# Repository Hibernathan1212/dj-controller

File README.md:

# DJ Controller

A MIDI jogless DJ controller similar to the Native Instruments S8 and D2 and X1 and Z1. Planning for it to just be a midi controller with knobs for mixing and controlling loops as well as buttons for play/pausing and others usually found on dj decks. Follows a modular design with the deck modules (2 on other side) and the mixer module which will have controls for 4 audio channels.

## Features

- Fully modular system
- 4 Audio track/channel support

## CAD

Consists of a base and a top lid that slots in a lip on the base. PCB is mounted to the lid with m2 screws that go into the faders and with the mx switches.

Onshape links:
[mixer](https://cad.onshape.com/documents/8781b8df6f967f1c6b6a95c1/w/5dca202985c09c767b10b646/e/c48e65838657ec88be66024d?renderMode=0&uiState=69ec6b3885827e36fd861eb5)
[deck](https://cad.onshape.com/documents/3b76899a1a1bc1a557b73df0/w/7b184ec473bdbf4286da5afb/e/11b981bd57d3e8bda80cba54?renderMode=0&uiState=69ec6bb0fbe7b2effac84fa0)

## PCB

Made in Kicad

### Schematic

### PCB

## Firmware

Uses python with the usb midi library and adafruit to take the GPIO input and send midi signals back to the computer.

# BOM

| Product                   | Amount | Unit Cost (THB) | Price (THB) | Price (USD) | Link                                                                                                                                                                                                                                                                                                                                                                                                                                                                                                                                                                                                                                                                                           |
| ------------------------- | ------ | --------------- | ----------- | ----------- | ---------------------------------------------------------------------------------------------------------------------------------------------------------------------------------------------------------------------------------------------------------------------------------------------------------------------------------------------------------------------------------------------------------------------------------------------------------------------------------------------------------------------------------------------------------------------------------------------------------------------------------------------------------------------------------------------- |
| CD74HC4067M               | 4      |                 | 57.82       | 1.788156353 | [https://th.aliexpress.com/item/1005006425003395.html](https://th.aliexpress.com/item/1005006425003395.html?spm=a2g0o.productlist.main.2.6875sBl8sBl8y9&algo_pvid=16e1eb5c-5f24-4909-9ec4-1832ca5d62b9&algo_exp_id=16e1eb5c-5f24-4909-9ec4-1832ca5d62b9-4&pdp_ext_f=%7B%22order%22%3A%2234%22%2C%22eval%22%3A%221%22%2C%22fromPage%22%3A%22search%22%7D&pdp_npi=6%40dis%21THB%21100.21%21100.21%21%21%2120.51%2120.51%21%402151e6dc17771029748282697e9e67%2112000037118555222%21sea%21TH%210%21ABX%211%210%21n_tag%3A-29910%3Bd%3A4d9dae13%3Bm03_new_user%3A-29895&curPageLogUid=p7QdqC5pT68Q&utparam-url=scene%3Asearch%7Cquery_from%3A%7Cx_object_id%3A1005006425003395%7C_p_origin_prod%3A) |
| bourn pta6043             | 2      | 62.9            | 125.8       | 3.890523508 | [https://th.element14.com/bourns/pta6043-2015dpb103/potentiometer-slide-10k-20-0-25w/dp/1688411](https://th.element14.com/bourns/pta6043-2015dpb103/potentiometer-slide-10k-20-0-25w/dp/1688411)                                                                                                                                                                                                                                                                                                                                                                                                                                                                                               |
| bourn pta4543             | 5      | 53.73           | 268.65      | 8.308339749 | [https://th.element14.com/bourns/pta4543-2015dpb103/potentiometer-slide-10k-45mm/dp/1688415](https://th.element14.com/bourns/pta4543-2015dpb103/potentiometer-slide-10k-45mm/dp/1688415)                                                                                                                                                                                                                                                                                                                                                                                                                                                                                                       |
| bourns ptv09a             | 27     | 23.36           | 630.72      | 19.50581071 | [https://th.element14.com/bourns/ptv09a-4020f-b103/pot-rotary-10kohm-9mm-20/dp/2469524](https://th.element14.com/bourns/ptv09a-4020f-b103/pot-rotary-10kohm-9mm-20/dp/2469524)                                                                                                                                                                                                                                                                                                                                                                                                                                                                                                                 |
| 100nf 0805 smd capacitors | 10     | 0.43            | 4.3         | 0.132982918 | [https://th.element14.com/multicomp-pro/mc0805b104k250ct/cap-0-1-f-25v-10-x7r-0805/dp/1759166](https://th.element14.com/multicomp-pro/mc0805b104k250ct/cap-0-1-f-25v-10-x7r-0805/dp/1759166)                                                                                                                                                                                                                                                                                                                                                                                                                                                                                                   |
| 6 alps ec11               | 6      | 81.42           | 488.52      | 15.10809654 | [https://th.element14.com/alps/ec11k1524402/encoder-vertical-11mm-30det-15ppr/dp/2064998](https://th.element14.com/alps/ec11k1524402/encoder-vertical-11mm-30det-15ppr/dp/2064998)                                                                                                                                                                                                                                                                                                                                                                                                                                                                                                             |
| m2 screws                 |        |                 | 154.17      | 4.767901504 | [https://th.element14.com/multicomp-pro/mp007338/screw-pan-head-pozidriv-m2-12mm/dp/3755264](https://th.element14.com/multicomp-pro/mp007338/screw-pan-head-pozidriv-m2-12mm/dp/3755264)                                                                                                                                                                                                                                                                                                                                                                                                                                                                                                       |
| orpheus pico              | 3      | ?               | ?           | 0           |                                                                                                                                                                                                                                                                                                                                                                                                                                                                                                                                                                                                                                                                                                |
| cherry switches           | 40     | 60              | 240         | 7.4223024   | [https://www.lazada.co.th/products/pdp-i5447727976-s23110798561.html](https://www.lazada.co.th/products/pdp-i5447727976-s23110798561.html)                                                                                                                                                                                                                                                                                                                                                                                                                                                                                                                                                     |
| cherry keycaps            | 38     | 280             | 560         | 17.3187056  | [https://www.lazada.co.th/products/lao8-20-key-xda-profile-pbt-keycaps-mechanical-keyboard-1u-1-x-ball-print-blank-customized-keycaps-mx-switches-xda-heighth-i16128506172-s127061437599.html?](https://www.lazada.co.th/products/lao8-20-key-xda-profile-pbt-keycaps-mechanical-keyboard-1u-1-x-ball-print-blank-customized-keycaps-mx-switches-xda-heighth-i16128506172-s127061437599.html?)                                                                                                                                                                                                                                                                                                 |
| 3d print filament         | 0.5    | 680             | 340         | 10.5149284  | [https://www.lazada.co.th/products/creality-hyper-petg-3d-printing-filament-1kg-175mm-plastic-filament-for-3d-printers-i5896245685-s126802674906.html?](https://www.lazada.co.th/products/creality-hyper-petg-3d-printing-filament-1kg-175mm-plastic-filament-for-3d-printers-i5896245685-s126802674906.html?)                                                                                                                                                                                                                                                                                                                                                                                 |
| jlcpcb                    |        |                 |             | 33.94       |                                                                                                                                                                                                                                                                                                                                                                                                                                                                                                                                                                                                                                                                                                |
| element 14 deliv          |        |                 | 550         | 17.009443   |                                                                                                                                                                                                                                                                                                                                                                                                                                                                                                                                                                                                                                                                                                |
|                           |        |                 |             |             |                                                                                                                                                                                                                                                                                                                                                                                                                                                                                                                                                                                                                                                                                                |
| total                     |        |                 |             | 139.7071907 |

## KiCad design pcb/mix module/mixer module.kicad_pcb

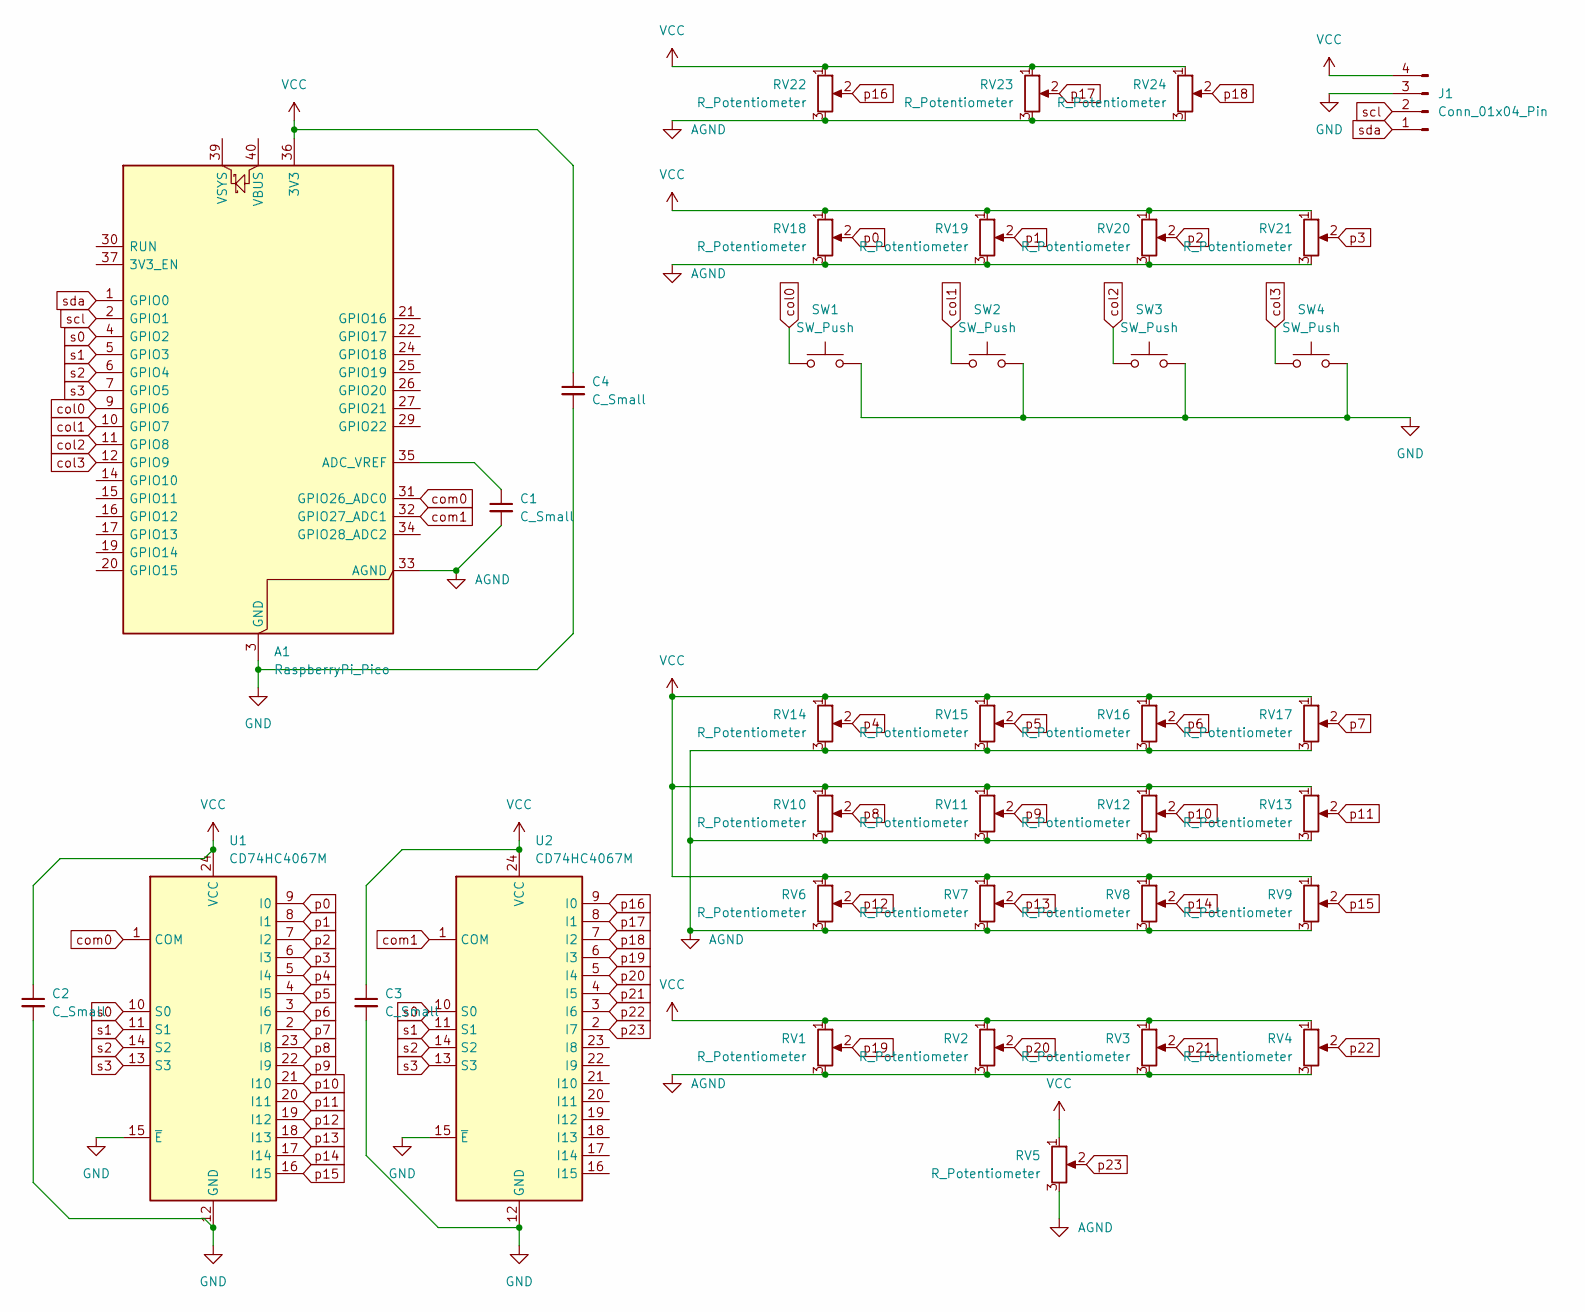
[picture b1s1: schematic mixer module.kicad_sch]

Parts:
A1: RaspberryPi_Pico; RaspberryPi_Pico_Common_Unspecified
C1, C2, C3, C4: C_Small; C_0805_2012Metric_Pad1.18x1.45mm_HandSolder
J1: Conn_01x04_Pin; ER_OLEDM0.91_1x-I2C
RV1, RV2, RV3, RV4, RV5: R_Potentiometer; Potentiometer_Bourns_PTA4543_Single_Slide
RV6, RV7, RV8, RV9, RV10, RV11, RV12, RV13, RV14, RV15, RV16, RV17, RV18, RV19, RV20, RV21, RV22, RV23, RV24: R_Potentiometer; Potentiometer_Bourns_PTV09A-1_Single_Vertical
SW1, SW2, SW3, SW4: SW_Push; SW_Cherry_MX_1.00u_PCB
U1, U2: CD74HC4067M; SOIC-24W_7.5x15.4mm_P1.27mm

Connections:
AGND: A1.33 (AGND), C1.2, RV1.3, RV2.3, RV3.3, RV4.3, RV5.3, RV6.3, RV7.3, RV8.3, RV9.3, RV10.3, RV11.3, RV12.3, RV13.3, RV14.3, RV15.3, RV16.3, RV17.3, RV18.3, RV19.3, RV20.3, RV21.3, RV22.3, RV23.3, RV24.3
GND: A1.3 (GND), A1.8 (GND), A1.13 (GND), A1.18 (GND), A1.23 (GND), A1.28 (GND), A1.38 (GND), C2.2, C3.2, C4.2, J1.3, SW1.2, SW2.2, SW3.2, SW4.2, U1.12 (GND), U1.15 (~E), U2.12 (GND), U2.15 (~E)
unnamed: A1.35 (ADC_VREF), C1.1
VCC: A1.36 (3V3), C2.1, C3.1, C4.1, J1.4, RV1.1, RV2.1, RV3.1, RV4.1, RV5.1, RV6.1, RV7.1, RV8.1, RV9.1, RV10.1, RV11.1, RV12.1, RV13.1, RV14.1, RV15.1, RV16.1, RV17.1, RV18.1, RV19.1, RV20.1, RV21.1, RV22.1, RV23.1, RV24.1, U1.24 (VCC), U2.24 (VCC)
col0: A1.9 (GPIO6), SW1.1
col1: A1.10 (GPIO7), SW2.1
col2: A1.11 (GPIO8), SW3.1
col3: A1.12 (GPIO9), SW4.1
com0: A1.31 (GPIO26_ADC0), U1.1 (COM)
com1: A1.32 (GPIO27_ADC1), U2.1 (COM)
p0: RV18.2, U1.9 (I0)
p1: RV19.2, U1.8 (I1)
p2: RV20.2, U1.7 (I2)
p3: RV21.2, U1.6 (I3)
p4: RV14.2, U1.5 (I4)
p5: RV15.2, U1.4 (I5)
p6: RV16.2, U1.3 (I6)
p7: RV17.2, U1.2 (I7)
p8: RV10.2, U1.23 (I8)
p9: RV11.2, U1.22 (I9)
p10: RV12.2, U1.21 (I10)
p11: RV13.2, U1.20 (I11)
p12: RV6.2, U1.19 (I12)
p13: RV7.2, U1.18 (I13)
p14: RV8.2, U1.17 (I14)
p15: RV9.2, U1.16 (I15)
p16: RV22.2, U2.9 (I0)
p17: RV23.2, U2.8 (I1)
p18: RV24.2, U2.7 (I2)
p19: RV1.2, U2.6 (I3)
p20: RV2.2, U2.5 (I4)
p21: RV3.2, U2.4 (I5)
p22: RV4.2, U2.3 (I6)
p23: RV5.2, U2.2 (I7)
s0: A1.4 (GPIO2), U1.10 (S0), U2.10 (S0)
s1: A1.5 (GPIO3), U1.11 (S1), U2.11 (S1)
s2: A1.6 (GPIO4), U1.14 (S2), U2.14 (S2)
s3: A1.7 (GPIO5), U1.13 (S3), U2.13 (S3)
scl: A1.2 (GPIO1), J1.2
sda: A1.1 (GPIO0), J1.1

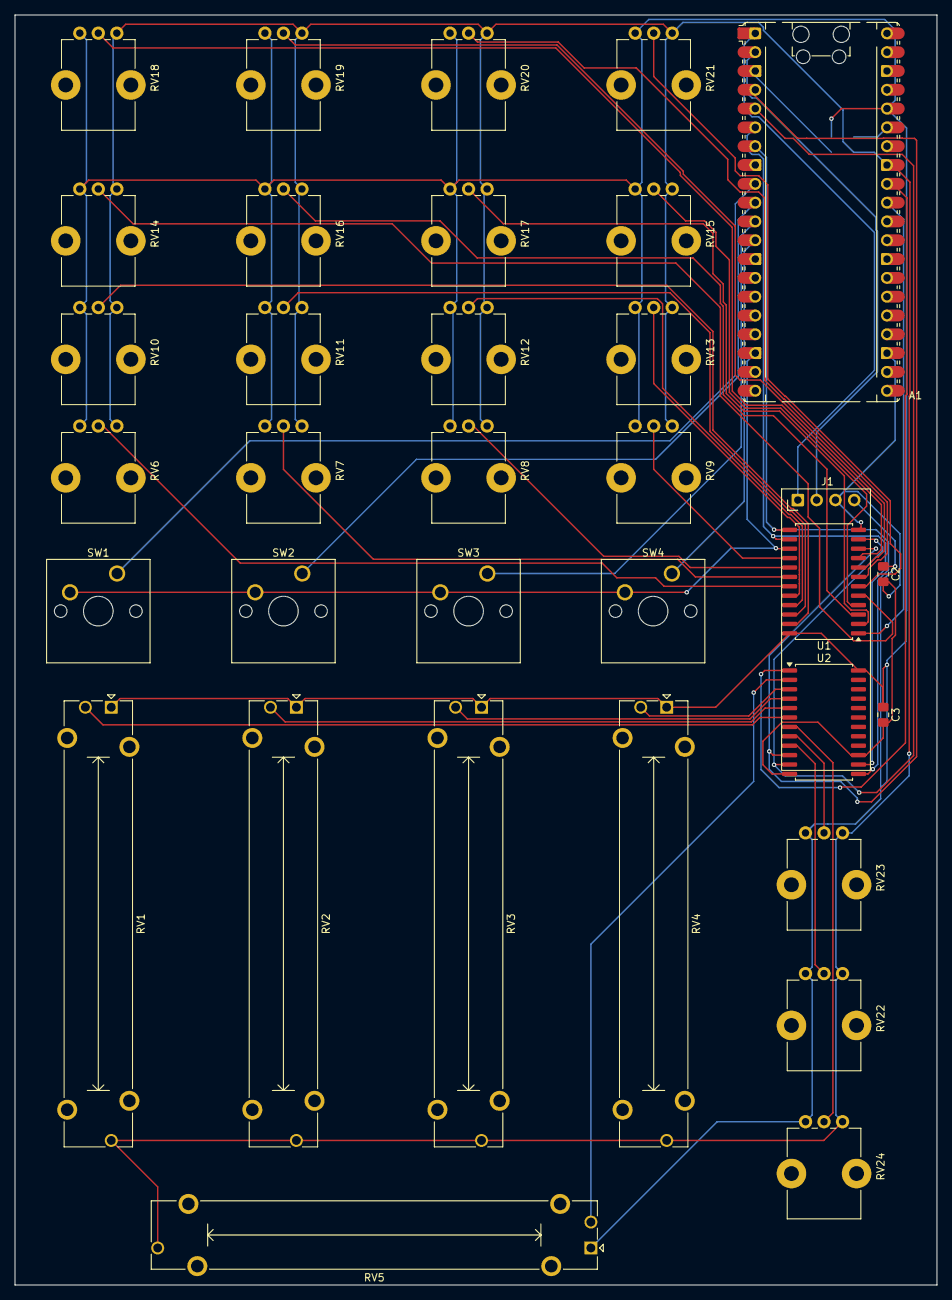
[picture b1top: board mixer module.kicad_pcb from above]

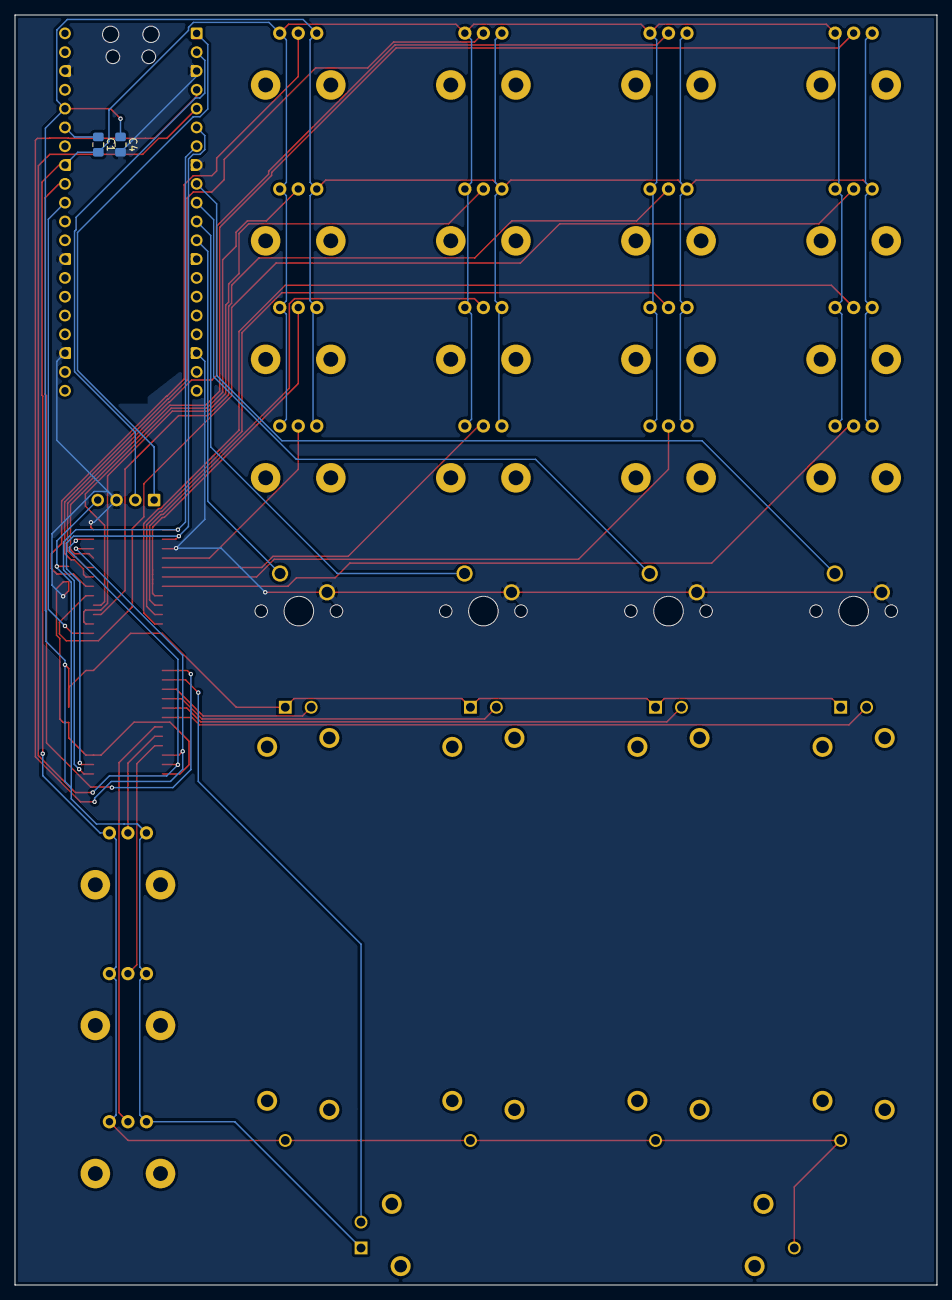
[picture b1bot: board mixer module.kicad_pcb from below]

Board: 2 copper layers, 124.5 x 171.5 mm, 36 parts (2 on the bottom side), 40 nets.

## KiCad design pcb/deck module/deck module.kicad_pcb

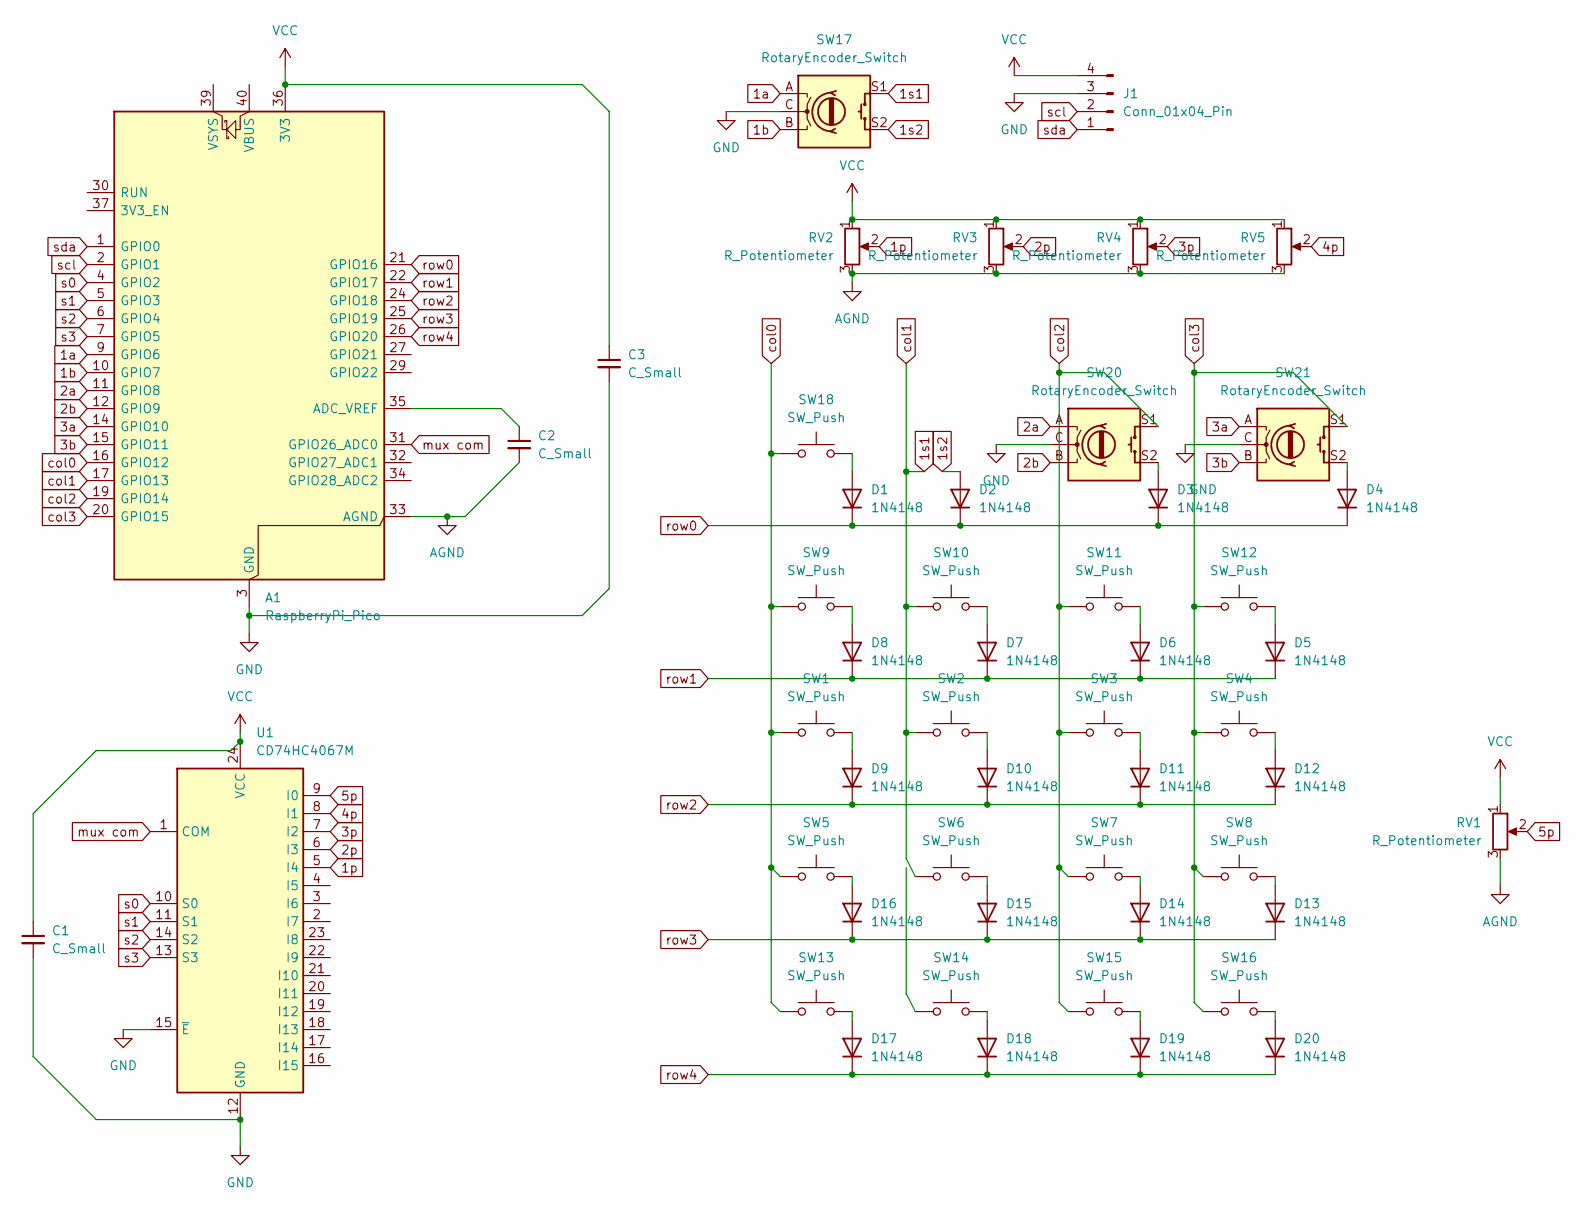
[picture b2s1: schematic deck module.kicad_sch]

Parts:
A1: RaspberryPi_Pico; RaspberryPi_Pico_Common_Unspecified
C1, C2, C3: C_Small; C_0805_2012Metric
D1, D2, D3, D4, D5, D6, D7, D8, D9, D10, D11, D12, D13, D14, D15, D16, D17, D18, D19, D20: 1N4148; D_DO-35_SOD27_P7.62mm_Horizontal
J1: Conn_01x04_Pin; ER_OLEDM0.91_1x-I2C
RV1: R_Potentiometer; Potentiometer_Bourns_PTA6043_Single_Slide
RV2, RV3, RV4, RV5: R_Potentiometer; Potentiometer_Bourns_PTV09A-1_Single_Vertical
SW1, SW2, SW3, SW4, SW5, SW6, SW7, SW8, SW9, SW10, SW11, SW12, SW13, SW14, SW15, SW16, SW18: SW_Push; SW_MX_1u
SW17, SW20, SW21: RotaryEncoder_Switch; RotaryEncoder_Alps_EC11E-Switch_Vertical_H20mm
U1: CD74HC4067M; SOIC-24W_7.5x15.4mm_P1.27mm

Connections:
1a: A1.9 (GPIO6), SW17.A
1b: A1.10 (GPIO7), SW17.B
1p: RV2.2, U1.5 (I4)
1s1: A1.17 (GPIO13), SW2.1, SW6.1, SW10.1, SW17.S1
1s2: D2.2 (A), SW17.S2
2a: A1.11 (GPIO8), SW20.A
2b: A1.12 (GPIO9), SW20.B
2p: RV3.2, U1.6 (I3)
3a: A1.14 (GPIO10), SW21.A
3b: A1.15 (GPIO11), SW21.B
3p: RV4.2, U1.7 (I2)
4p: RV5.2, U1.8 (I1)
5p: RV1.2, U1.9 (I0)
AGND: A1.33 (AGND), C2.2, RV1.3, RV2.3, RV3.3, RV4.3, RV5.3
GND: A1.3 (GND), A1.8 (GND), A1.13 (GND), A1.18 (GND), A1.23 (GND), A1.28 (GND), A1.38 (GND), C1.2, C3.2, J1.3, SW17.C, SW20.C, SW21.C, U1.12 (GND), U1.15 (~E)
unnamed: A1.35 (ADC_VREF), C2.1
unnamed: D1.2 (A), SW18.2
unnamed: D3.2 (A), SW20.S2
unnamed: D4.2 (A), SW21.S2
unnamed: D5.2 (A), SW12.2
unnamed: D6.2 (A), SW11.2
unnamed: D7.2 (A), SW10.2
unnamed: D8.2 (A), SW9.2
unnamed: D9.2 (A), SW1.2
unnamed: D10.2 (A), SW2.2
unnamed: D11.2 (A), SW3.2
unnamed: D12.2 (A), SW4.2
unnamed: D13.2 (A), SW8.2
unnamed: D14.2 (A), SW7.2
unnamed: D15.2 (A), SW6.2
unnamed: D16.2 (A), SW5.2
unnamed: D17.2 (A), SW13.2
unnamed: D18.2 (A), SW14.2 (2_2)
unnamed: D19.2 (A), SW15.2
unnamed: D20.2 (A), SW16.2
VCC: A1.36 (3V3), C1.1, C3.1, J1.4, RV1.1, RV2.1, RV3.1, RV4.1, RV5.1, U1.24 (VCC)
col0: A1.16 (GPIO12), SW1.1, SW5.1, SW9.1, SW13.1, SW18.1
col2: A1.19 (GPIO14), SW3.1, SW7.1, SW11.1, SW15.1, SW20.S1
col3: A1.20 (GPIO15), SW4.1, SW8.1, SW12.1, SW16.1, SW21.S1
mux com: A1.31 (GPIO26_ADC0), U1.1 (COM)
row0: A1.21 (GPIO16), D1.1 (K), D2.1 (K), D3.1 (K), D4.1 (K)
row1: A1.22 (GPIO17), D5.1 (K), D6.1 (K), D7.1 (K), D8.1 (K)
row2: A1.24 (GPIO18), D9.1 (K), D10.1 (K), D11.1 (K), D12.1 (K)
row3: A1.25 (GPIO19), D13.1 (K), D14.1 (K), D15.1 (K), D16.1 (K)
row4: A1.26 (GPIO20), D17.1 (K), D18.1 (K), D19.1 (K), D20.1 (K)
s0: A1.4 (GPIO2), U1.10 (S0)
s1: A1.5 (GPIO3), U1.11 (S1)
s2: A1.6 (GPIO4), U1.14 (S2)
s3: A1.7 (GPIO5), U1.13 (S3)
scl: A1.2 (GPIO1), J1.2
sda: A1.1 (GPIO0), J1.1

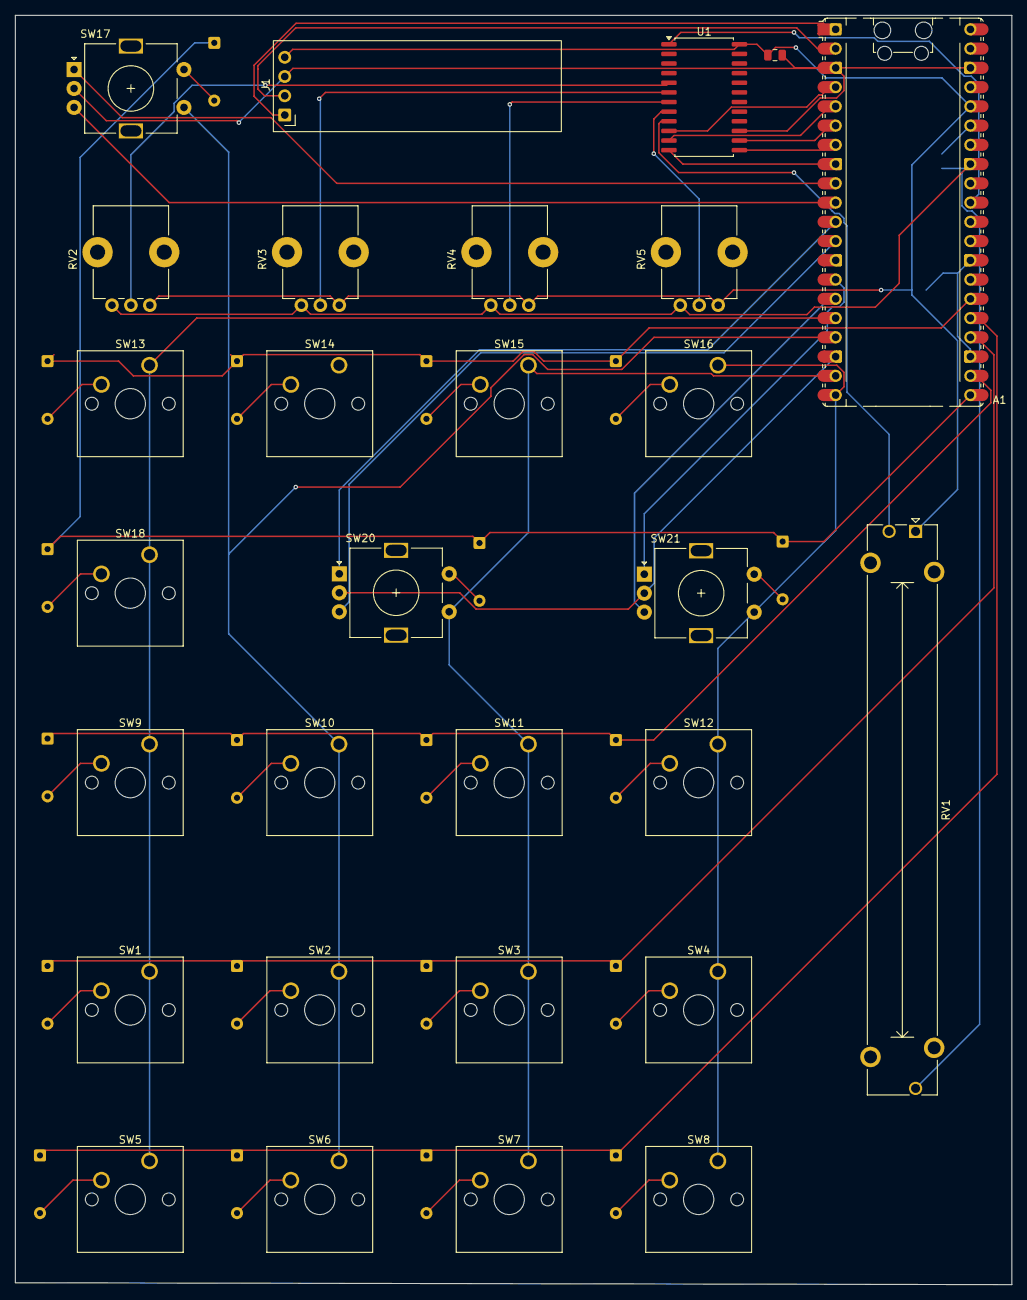
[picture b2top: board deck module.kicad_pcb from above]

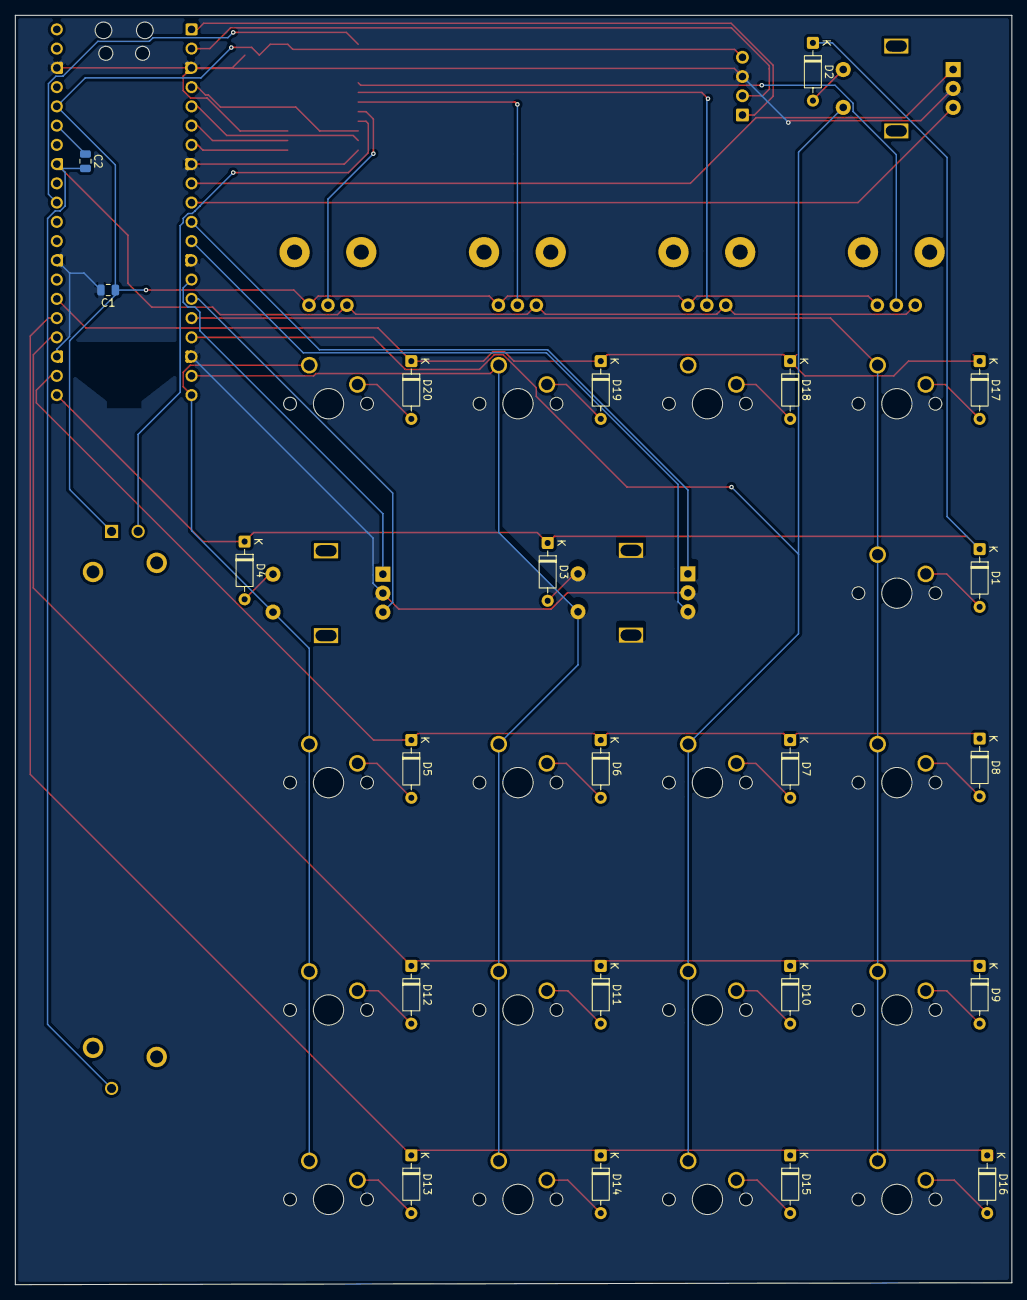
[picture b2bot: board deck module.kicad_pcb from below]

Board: 2 copper layers, 131.5 x 167.5 mm, 51 parts (22 on the bottom side), 51 nets.

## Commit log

2026-04-01 init commit
2026-04-25 add cad
